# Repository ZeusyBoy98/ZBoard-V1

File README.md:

# ZBoard-V1
Video: https://github.com/ZeusyBoy98/ZBoard-V1/blob/main/IMG/ZBoard-V1-Video.mp4.  
The ultimate minimalistic 75% low-profile keyboard that fits my needs!
Made for Hack Club Fallout.

## Zine

## What does it do?
It's a 75% low-profile keyboard with Gateron KS33 Chocolate Switches, NuPhy COAST Twilight Keycaps, and a 3D printed shell and plate.

## Why?
Because I hate my current keyboard options. I have a Corsair K70 Core which sucks for anything other than gaming, and some old HP keyboard which doesn't register switch presses half the time. So I decided to build my own keyboard. My requirements were for it to be low profile & 75%, so it can fit anywere for any situation, and use switches which I really enjoy pressing. In the end, this is the design I came up with and I could not be happier.

## Motivation
I don't have a good keyboard. My options are a gaming keyboard that double presses, or a membrane keyboard that doesn't press. This should fix both those issues and be actually enjoyable to use.

## How?
In order to make this project for yourself, you'll need to purchase/3D print the items in the bill of materials below.

| Qty      | Component                     | Link                                                                                                         | Price Individual (USD)        | Price Sum (USD)           |
| -------- | ----------------------------- | ------------------------------------------------------------------------------------------------------------ | ----------------------------- | ------------------------- |
| 100      | Diode                         | [LCSC](https://www.lcsc.com/product-detail/C917030.html?s_z=n_1N4148W)                                       | 0.0058                        | 0.58                      |
| 1        | Switches (110 KS33 Chocolate) | [Gateron](https://www.gateron.com/products/gateron-ks-33-low-profile-20-chocolate-switch?VariantsId=11140)   | 39.60                         | 39.60                     |
| 1        | Hotswap Sockets               | [Gateron](https://www.gateron.com/products/gateron-low-profile-switch-hot-swap-pcb-socket?VariantsId=10234)  | 11.00                         | 11.00                     |
| 1        | Stabilizers                   | [Gateron](https://www.gateron.com/products/gateron-low-profile-plate-mounted-stabilizer?VariantsId=10540)    | 8.00                          | 8.00                      |
| 1        | Orpheus Pico                  | Hack Club Flavourtown                                                                                        | Already owned                 | Already owned             |
| 1        | Heat set insert               | [Core Electronics](https://core-electronics.com.au/brass-heat-set-inserts-for-plastic-m3-x-3mm-50-pack.html) | Already owned                 | (8.39)                    |
| 1        | 5mm M3 Screw                  | [Core Electronics](https://core-electronics.com.au/machine-screw-m3-5mm-length-phillips-25-pack.html)        | Already owned                 | (2.24)                    |
| 1        | Case Pieces                   | CAD/ZBoard-V1-Print.3mf                                                                                      | 3D printing (220g filament)   |                           |
| 1        | Keycap Set                    | CAD/ZBoard-V1-Print.3mf                                                                                      | 3D printing<br>(70g filament) | (Total 3D printing: 4.61) |
| 1        | PCB                           | PCB/production/ZBoard_V1.zip                                                                                 |                               | 21.90                     |
| Shipping |                               |                                                                                                              |                               | 8.60+21.28+10.77=40.65    |
| Total    |                               |                                                                                                              |                               | 99.83                     |

### Build Guide:

#### 1. Preparation<br>
Before starting, make sure you have:
<ul>
<li>All components from the BOM
<li>A soldering iron + solder
<li>Tweezers (there are lots of small components)
<li>Flux (helpful)
<li>A screwdriver
<li>A 3D printer (or get the printed parts from someone else) - Print file at CAD/ZBoard-v1-Print.3mf
</ul>

#### 2. Soldering
Take your pcb and begin soldering components to it<br>
Recommended order:
<ul>
<li>SMD Components (Diodes, hot swap sockets)
<li>Microcontroller (Orpheus Pico)
</ul>

#### 3. Switches + Stabilizers
Insert each individual keyboard switch first, then do the stabilizers. Make sure every switch is properly seated in the socket.

#### 4. Case + Keycaps
<ul>
<li>3D print the case pieces and keycaps.
<li>Insert heat-set inserts with soldering iron into holes in bottom part of case.
<li>Place PCB into case and screw case closed with M3 Screws
<li>Put keycaps onto switches
</ul>

#### 5. Flash ZMK firmware
<ul>
<li>Plug the keyboard in via USB
<li>Double press the boot button to enter bootloader
<li>A new USB drive will appear
<li>Copy Firmware/zboard_zboardv1_default.uf2 onto the new USB drive
<li>Wait for Firmware to finish flashing
</ul>

Enjoy your ZBoard!

## Video

## Renders
Note: these renders are from the old version so they don't show the pi pico

## Designing

Here's the version with more personality:

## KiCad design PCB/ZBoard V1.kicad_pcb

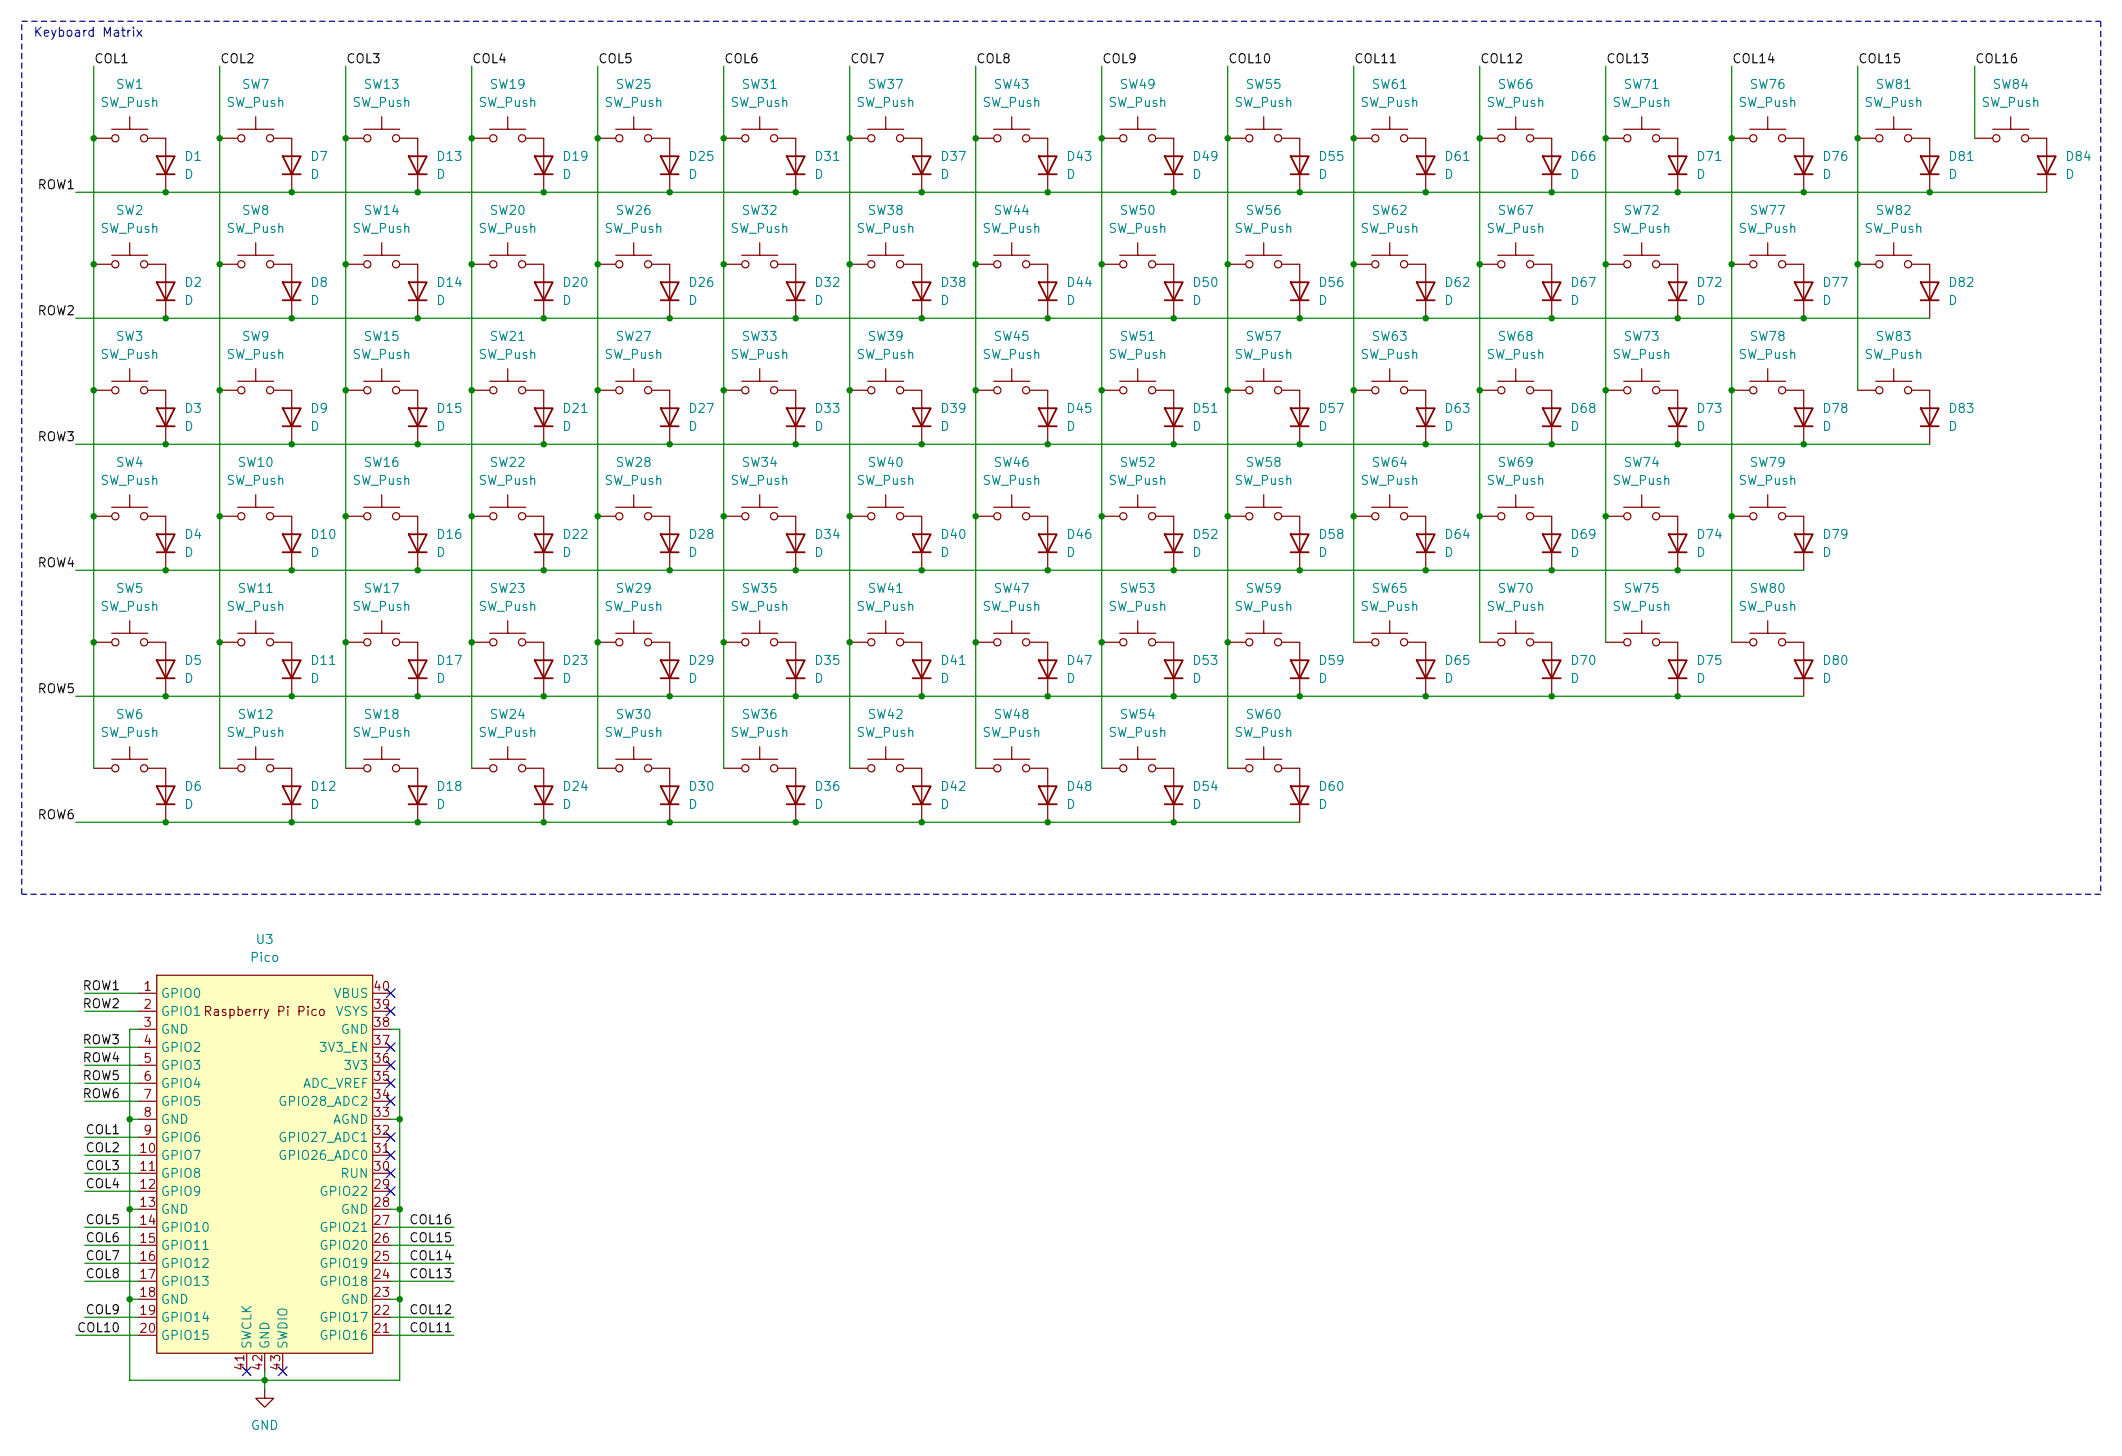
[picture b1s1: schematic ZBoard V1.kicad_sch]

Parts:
D1, D2, D3, D4, D5, D6, D7, D8, D9, D10, D11, D12, D13, D14, D15, D16, D17, D18, D19, D20, D21, D22, D23, D24, D25, D26, D27, D28, D29, D30, D31, D32, D33, D34, D35, D36, D37, D38, D39, D40, D41, D42, D43, D44, D45, D46, D47, D48, D49, D50, D51, D52, D53, D54, D55, D56, D57, D58, D59, D60, D61, D62, D63, D64, D65, D66, D67, D68, D69, D70, D71, D72, D73, D74, D75, D76, D77, D78, D79, D80, D81, D82, D83, D84: D; D_SOD-123
SW1, SW2, SW7, SW8, SW9, SW10, SW11, SW13, SW14, SW15, SW16, SW17, SW19, SW20, SW21, SW22, SW23, SW25, SW26, SW27, SW28, SW29, SW30, SW31, SW32, SW33, SW34, SW35, SW36, SW37, SW38, SW39, SW40, SW41, SW42, SW43, SW44, SW45, SW46, SW47, SW48, SW49, SW50, SW51, SW52, SW53, SW54, SW55, SW56, SW57, SW58, SW59, SW60, SW61, SW62, SW63, SW64, SW65, SW66, SW67, SW68, SW69, SW71, SW72, SW73, SW75, SW76, SW79, SW80, SW81, SW82, SW83, SW84: SW_Push; Gateron-KS33-Hotswap-1U
SW3, SW78: SW_Push; Gateron-KS33-Hotswap-1.5U
SW4, SW70: SW_Push; Gateron-KS33-Hotswap-1.75U
SW5, SW74: SW_Push; Gateron-KS33-Hotswap-2.25U
SW6, SW12, SW18: SW_Push; Gateron-KS33-Hotswap-1.25U
SW24: SW_Push; Gateron-KS33-Hotswap-6.25U
SW77: SW_Push; Gateron-KS33-Hotswap-2U
U3: Pico; RPi_Pico_SMD_TH

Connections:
/COL1: SW1.1, SW2.1, SW3.1, SW4.1, SW5.1, SW6.1, U3.9 (GPIO6)
/COL2: SW7.1, SW8.1, SW9.1, SW10.1, SW11.1, SW12.1, U3.10 (GPIO7)
/COL3: SW13.1, SW14.1, SW15.1, SW16.1, SW17.1, SW18.1, U3.11 (GPIO8)
/COL4: SW19.1, SW20.1, SW21.1, SW22.1, SW23.1, SW24.1, U3.12 (GPIO9)
/COL5: SW25.1, SW26.1, SW27.1, SW28.1, SW29.1, SW30.1, U3.14 (GPIO10)
/COL6: SW31.1, SW32.1, SW33.1, SW34.1, SW35.1, SW36.1, U3.15 (GPIO11)
/COL7: SW37.1, SW38.1, SW39.1, SW40.1, SW41.1, SW42.1, U3.16 (GPIO12)
/COL8: SW43.1, SW44.1, SW45.1, SW46.1, SW47.1, SW48.1, U3.17 (GPIO13)
/COL9: SW49.1, SW50.1, SW51.1, SW52.1, SW53.1, SW54.1, U3.19 (GPIO14)
/COL10: SW55.1, SW56.1, SW57.1, SW58.1, SW59.1, SW60.1, U3.20 (GPIO15)
/COL11: SW61.1, SW62.1, SW63.1, SW64.1, SW65.1, U3.21 (GPIO16)
/COL12: SW66.1, SW67.1, SW68.1, SW69.1, SW70.1, U3.22 (GPIO17)
/COL13: SW71.1, SW72.1, SW73.1, SW74.1, SW75.1, U3.24 (GPIO18)
/COL14: SW76.1, SW77.1, SW78.1, SW79.1, SW80.1, U3.25 (GPIO19)
/COL15: SW81.1, SW82.1, SW83.1, U3.26 (GPIO20)
/COL16: SW84.1, U3.27 (GPIO21)
/ROW1: D1.1 (K), D7.1 (K), D13.1 (K), D19.1 (K), D25.1 (K), D31.1 (K), D37.1 (K), D43.1 (K), D49.1 (K), D55.1 (K), D61.1 (K), D66.1 (K), D71.1 (K), D76.1 (K), D81.1 (K), D84.1 (K), U3.1 (GPIO0)
/ROW2: D2.1 (K), D8.1 (K), D14.1 (K), D20.1 (K), D26.1 (K), D32.1 (K), D38.1 (K), D44.1 (K), D50.1 (K), D56.1 (K), D62.1 (K), D67.1 (K), D72.1 (K), D77.1 (K), D82.1 (K), U3.2 (GPIO1)
/ROW3: D3.1 (K), D9.1 (K), D15.1 (K), D21.1 (K), D27.1 (K), D33.1 (K), D39.1 (K), D45.1 (K), D51.1 (K), D57.1 (K), D63.1 (K), D68.1 (K), D73.1 (K), D78.1 (K), D83.1 (K), U3.4 (GPIO2)
/ROW4: D4.1 (K), D10.1 (K), D16.1 (K), D22.1 (K), D28.1 (K), D34.1 (K), D40.1 (K), D46.1 (K), D52.1 (K), D58.1 (K), D64.1 (K), D69.1 (K), D74.1 (K), D79.1 (K), U3.5 (GPIO3)
/ROW5: D5.1 (K), D11.1 (K), D17.1 (K), D23.1 (K), D29.1 (K), D35.1 (K), D41.1 (K), D47.1 (K), D53.1 (K), D59.1 (K), D65.1 (K), D70.1 (K), D75.1 (K), D80.1 (K), U3.6 (GPIO4)
/ROW6: D6.1 (K), D12.1 (K), D18.1 (K), D24.1 (K), D30.1 (K), D36.1 (K), D42.1 (K), D48.1 (K), D54.1 (K), D60.1 (K), U3.7 (GPIO5)
GND: U3.3 (GND), U3.8 (GND), U3.13 (GND), U3.18 (GND), U3.23 (GND), U3.28 (GND), U3.33 (AGND), U3.38 (GND), U3.42 (GND)
unnamed: D1.2 (A), SW1.2
unnamed: D2.2 (A), SW2.2
unnamed: D3.2 (A), SW3.2
unnamed: D4.2 (A), SW4.2
unnamed: D5.2 (A), SW5.2
unnamed: D6.2 (A), SW6.2
unnamed: D7.2 (A), SW7.2
unnamed: D8.2 (A), SW8.2
unnamed: D9.2 (A), SW9.2
unnamed: D10.2 (A), SW10.2
unnamed: D11.2 (A), SW11.2
unnamed: D12.2 (A), SW12.2
unnamed: D13.2 (A), SW13.2
unnamed: D14.2 (A), SW14.2
unnamed: D15.2 (A), SW15.2
unnamed: D16.2 (A), SW16.2
unnamed: D17.2 (A), SW17.2
unnamed: D18.2 (A), SW18.2
unnamed: D19.2 (A), SW19.2
unnamed: D20.2 (A), SW20.2
unnamed: D21.2 (A), SW21.2
unnamed: D22.2 (A), SW22.2
unnamed: D23.2 (A), SW23.2
unnamed: D24.2 (A), SW24.2
unnamed: D25.2 (A), SW25.2
unnamed: D26.2 (A), SW26.2
unnamed: D27.2 (A), SW27.2
unnamed: D28.2 (A), SW28.2
unnamed: D29.2 (A), SW29.2
unnamed: D30.2 (A), SW30.2
unnamed: D31.2 (A), SW31.2
unnamed: D32.2 (A), SW32.2
unnamed: D33.2 (A), SW33.2
unnamed: D34.2 (A), SW34.2
unnamed: D35.2 (A), SW35.2
unnamed: D36.2 (A), SW36.2
unnamed: D37.2 (A), SW37.2
unnamed: D38.2 (A), SW38.2
unnamed: D39.2 (A), SW39.2
unnamed: D40.2 (A), SW40.2
unnamed: D41.2 (A), SW41.2
unnamed: D42.2 (A), SW42.2
unnamed: D43.2 (A), SW43.2
unnamed: D44.2 (A), SW44.2
unnamed: D45.2 (A), SW45.2
unnamed: D46.2 (A), SW46.2
unnamed: D47.2 (A), SW47.2
unnamed: D48.2 (A), SW48.2
unnamed: D49.2 (A), SW49.2
unnamed: D50.2 (A), SW50.2
unnamed: D51.2 (A), SW51.2
unnamed: D52.2 (A), SW52.2
unnamed: D53.2 (A), SW53.2
unnamed: D54.2 (A), SW54.2
unnamed: D55.2 (A), SW55.2
unnamed: D56.2 (A), SW56.2
unnamed: D57.2 (A), SW57.2
unnamed: D58.2 (A), SW58.2
unnamed: D59.2 (A), SW59.2
unnamed: D60.2 (A), SW60.2
unnamed: D61.2 (A), SW61.2
unnamed: D62.2 (A), SW62.2
unnamed: D63.2 (A), SW63.2
unnamed: D64.2 (A), SW64.2
unnamed: D65.2 (A), SW65.2
unnamed: D66.2 (A), SW66.2
unnamed: D67.2 (A), SW67.2
unnamed: D68.2 (A), SW68.2
unnamed: D69.2 (A), SW69.2
unnamed: D70.2 (A), SW70.2
unnamed: D71.2 (A), SW71.2
unnamed: D72.2 (A), SW72.2
unnamed: D73.2 (A), SW73.2
unnamed: D74.2 (A), SW74.2
unnamed: D75.2 (A), SW75.2
unnamed: D76.2 (A), SW76.2
unnamed: D77.2 (A), SW77.2
unnamed: D78.2 (A), SW78.2
unnamed: D79.2 (A), SW79.2
unnamed: D80.2 (A), SW80.2
unnamed: D81.2 (A), SW81.2
unnamed: D82.2 (A), SW82.2
unnamed: D83.2 (A), SW83.2
unnamed: D84.2 (A), SW84.2

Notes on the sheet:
Keyboard Matrix

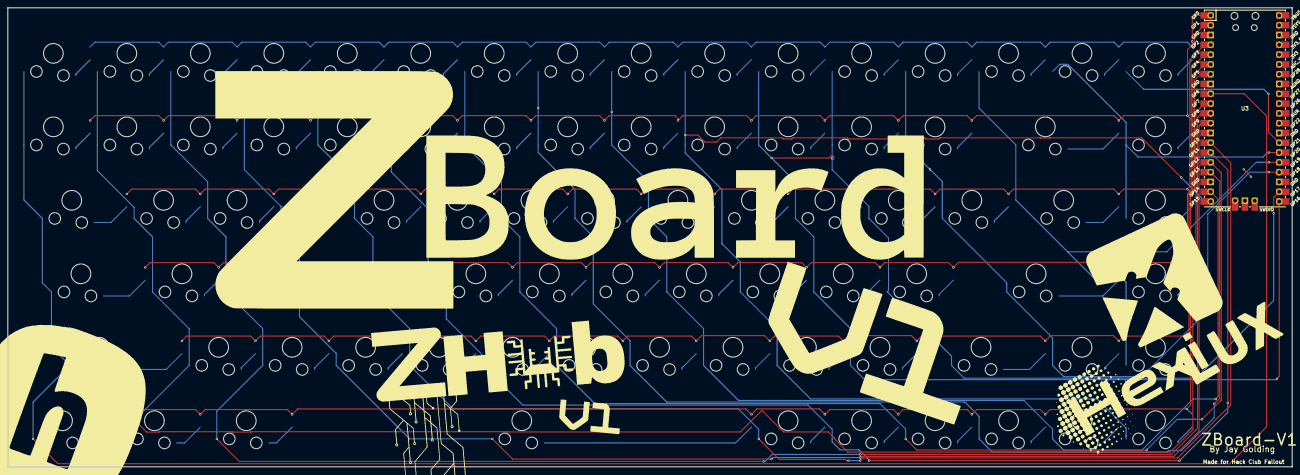
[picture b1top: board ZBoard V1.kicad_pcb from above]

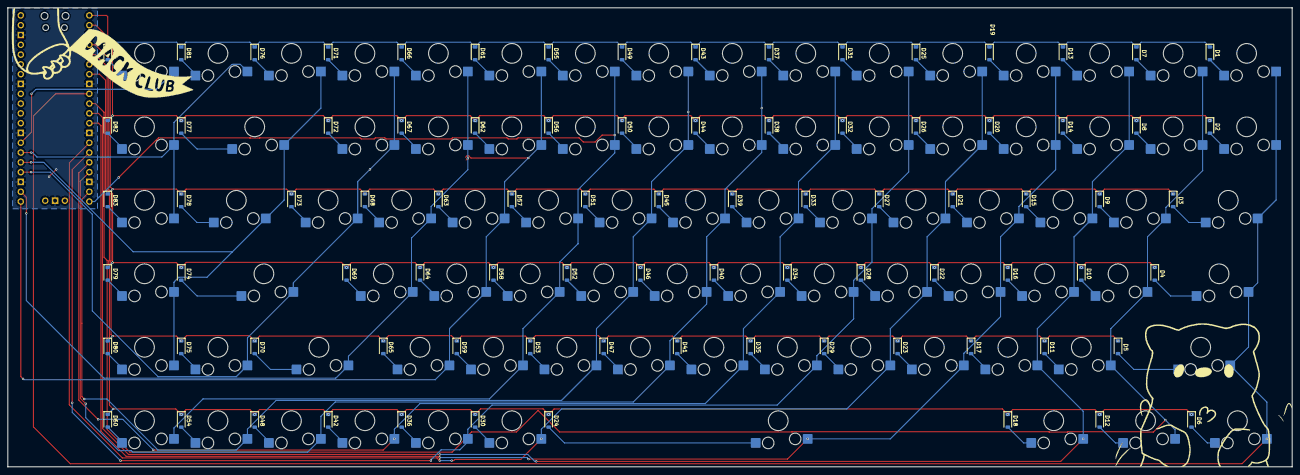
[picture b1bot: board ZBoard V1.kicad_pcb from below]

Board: 2 copper layers, 333.0 x 119.0 mm, 169 parts (168 on the bottom side), 107 nets.

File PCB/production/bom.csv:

Designator,Footprint,Quantity,Value,LCSC Part #
"D1, D10, D11, D12, D13, D14, D15, D16, D17, D18, D19, D2, D20, D21, D22, D23, D24, D25, D26, D27, D28, D29, D3, D30, D31, D32, D33, D34, D35, D36, D37, D38, D39, D4, D40, D41, D42, D43, D44, D45, D46, D47, D48, D49, D5, D50, D51, D52, D53, D54, D55, D56, D57, D58, D59, D6, D60, D61, D62, D63, D64, D65, D66, D67, D68, D69, D7, D70, D71, D72, D73, D74, D75, D76, D77, D78, D79, D8, D80, D81, D82, D83, D84, D9",D_SOD-123,84,D,
"SW1, SW10, SW11, SW13, SW14, SW15, SW16, SW17, SW19, SW2, SW20, SW21, SW22, SW23, SW25, SW26, SW27, SW28, SW29, SW30, SW31, SW32, SW33, SW34, SW35, SW36, SW37, SW38, SW39, SW40, SW41, SW42, SW43, SW44, SW45, SW46, SW47, SW48, SW49, SW50, SW51, SW52, SW53, SW54, SW55, SW56, SW57, SW58, SW59, SW60, SW61, SW62, SW63, SW64, SW65, SW66, SW67, SW68, SW69, SW7, SW71, SW72, SW73, SW75, SW76, SW79, SW8, SW80, SW81, SW82, SW83, SW84, SW9",Gateron-KS33-Hotswap-1U,73,SW_Push,
"SW12, SW18, SW6",Gateron-KS33-Hotswap-1.25U,3,SW_Push,
SW24,Gateron-KS33-Hotswap-6.25U,1,SW_Push,
"SW3, SW78",Gateron-KS33-Hotswap-1.5U,2,SW_Push,
"SW4, SW70",Gateron-KS33-Hotswap-1.75U,2,SW_Push,
"SW5, SW74",Gateron-KS33-Hotswap-2.25U,2,SW_Push,
SW77,Gateron-KS33-Hotswap-2U,1,SW_Push,
U3,RPi_Pico_SMD_TH,1,Pico,

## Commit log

2026-03-17 Add PCB files
2026-03-18 Change to 75% keyboard layout and move around PCB files
2026-03-19 Finish PCB routing
2026-03-21 Fix typo (thx brake)
2026-03-21 Reroute with switches on correct side
2026-03-22 Add BOM
2026-03-22 Update BOM with keycaps
2026-03-22 Complete case, update BOM, start rendering images
2026-03-25 BOM + Case + Images & Video
2026-03-25 Rename images
2026-03-25 Better readme
2026-03-25 Fix file names for readme
2026-03-25 Fix file names for readme again
2026-03-25 Reformat image section in readme
2026-03-25 Update BOM
2026-03-25 Add Journal.md and add progress
2026-03-25 Add new render to readme
2026-03-28 Firmware. The largest pain in the world.
2026-03-31 Update journal up to March 28th
2026-03-31 Added fancy silkscreen
2026-04-02 Added Zine
2026-04-03 Changed to 3D printed keycaps, changed parts sourcing, modified BOM
2026-04-04 Fixed pinouts, fixed firmware
2026-04-04 Add built firmware
2026-04-04 Update BOM and Journal
2026-04-04 Fix BOM for shipping
2026-04-04 Fixed BOM, added CAD source files, and added build guide.
2026-04-04 Removing CAD source files
2026-04-04 Readding CAD source files
2026-04-04 Fix the issues pls work
2026-04-04 Reformat build guide pls work...
2026-04-04 Add much more comprehensive build guide
2026-04-25 Fix problems for fallout resubmission
2026-05-30 Beginning transition to wired using Orpheus Pico
2026-06-01 Finally got working firmware
2026-06-01 Final commit pls
2026-06-01 Fix bootloader instructions
2026-06-06 Make changes for resubmission (surely this time)
2026-06-06 Make changes for resubmission
2026-06-06 Gif added through lfs
2026-06-07 Add more 'personality'
